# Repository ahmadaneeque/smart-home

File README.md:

# smart-home
dependencies 
- PainlessMesh to handel the mesh archetecture <https://github.com/gmag11/painlessMesh>
- WiFiManager to manage the credentials / https://github.com/tzapu/WiFiManager
- ArduinoJson to parse data https://github.com/bblanchon/ArduinoJson

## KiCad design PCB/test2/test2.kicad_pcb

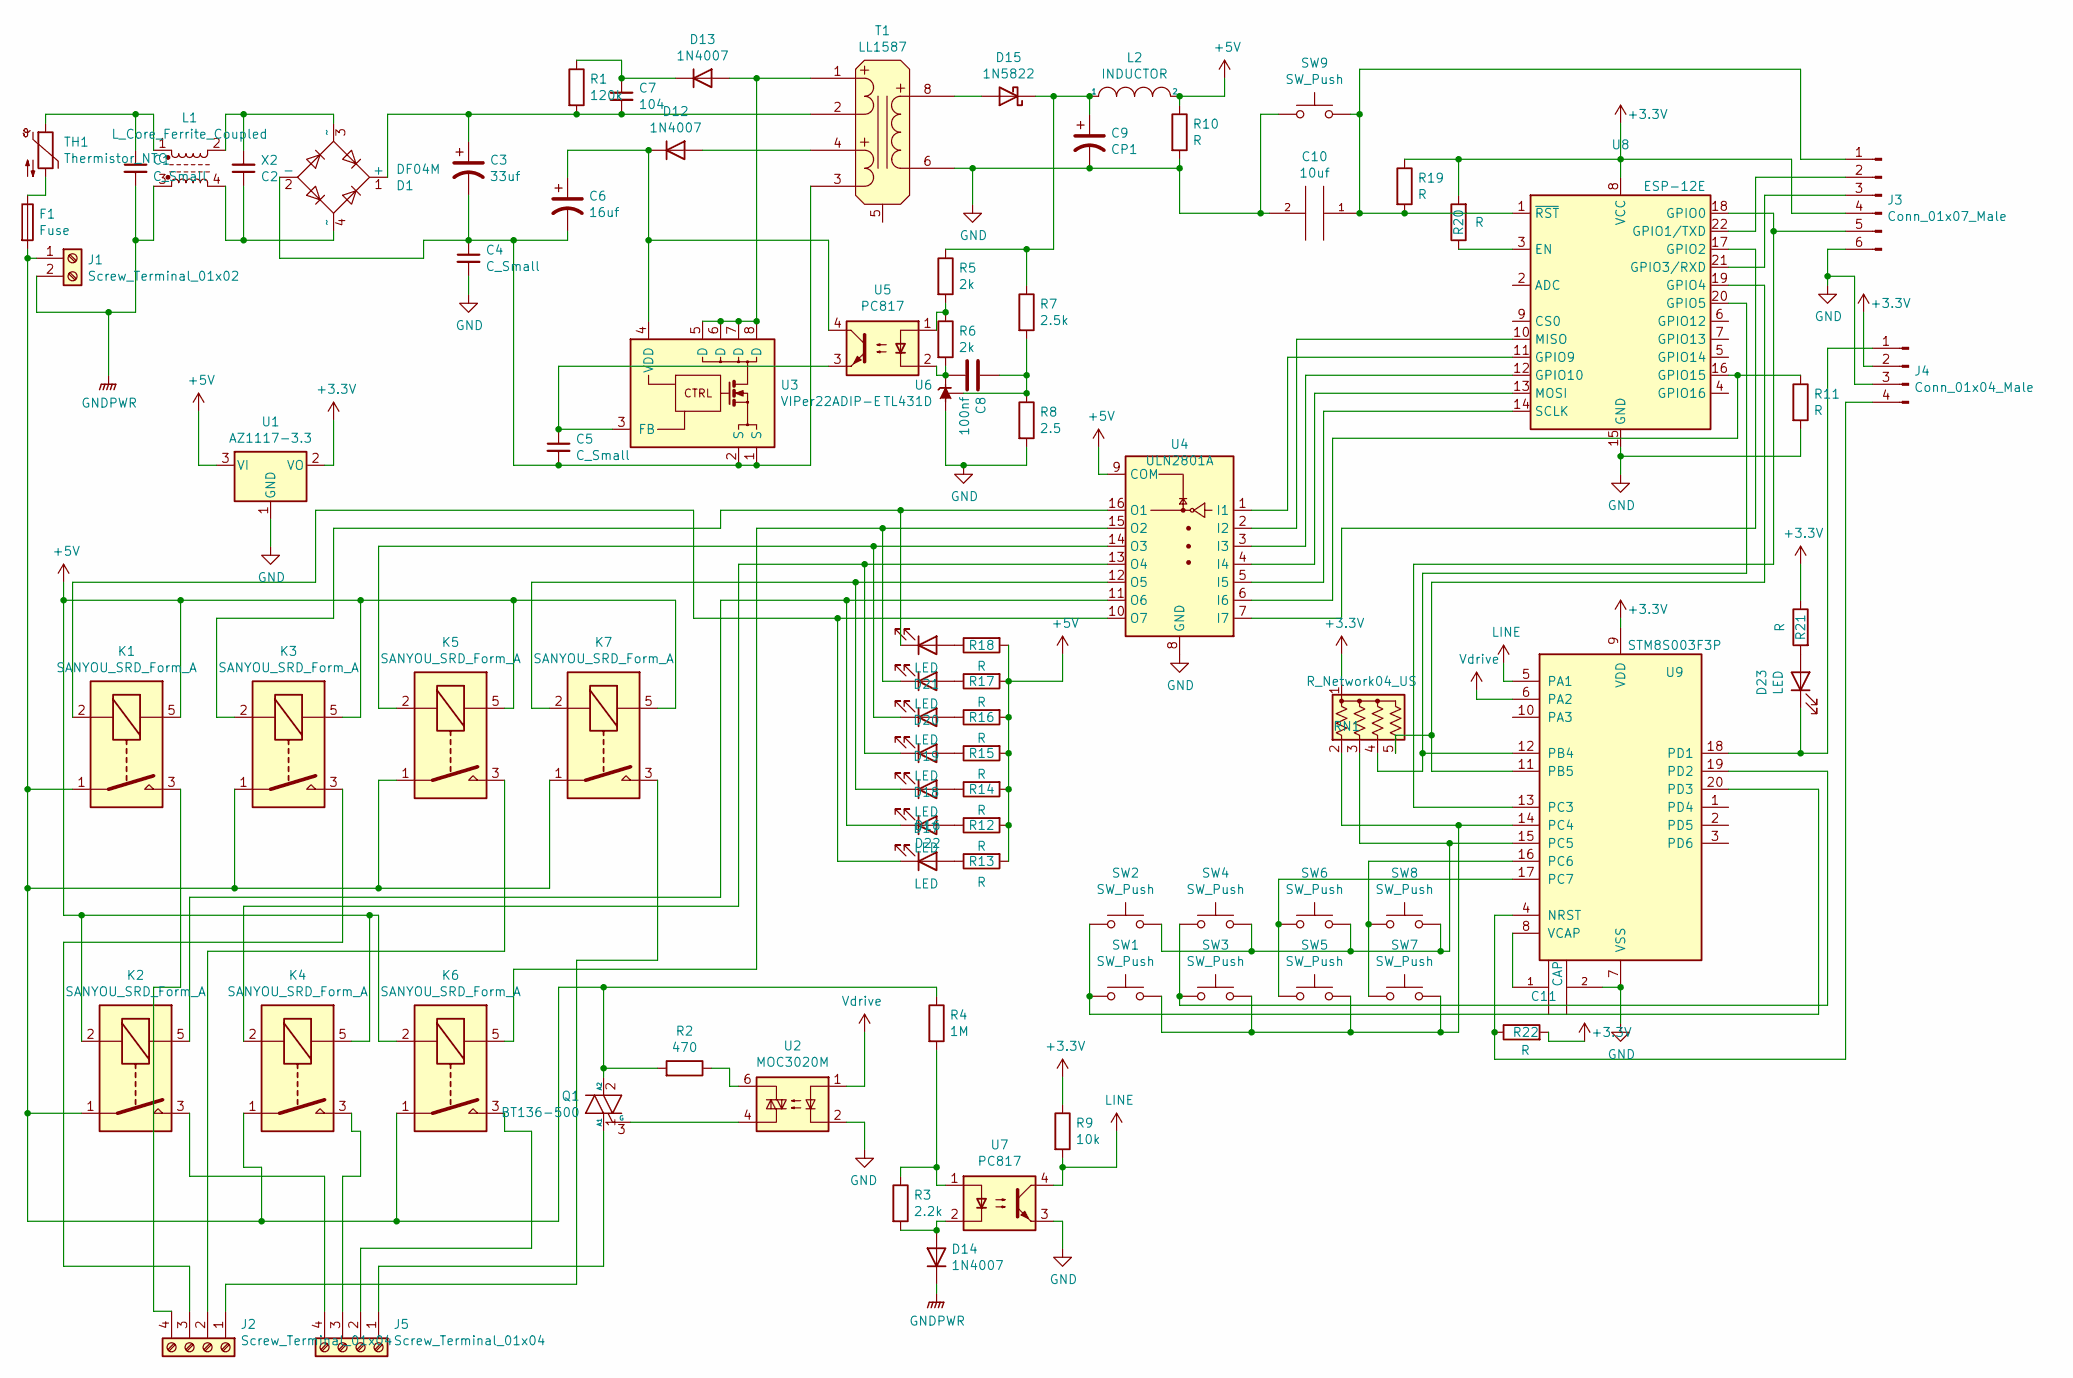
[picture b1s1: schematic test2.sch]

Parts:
C1: C_Small; RV_Disc_D7mm_W3.5mm_P5mm
C2: X2; CP_Axial_L10.0mm_D6.0mm_P15.00mm_Horizontal
C3: 33uf; CP_Radial_D10.0mm_P5.00mm_P7.50mm
C4: C_Small; C_Disc_D10.5mm_W5.0mm_P7.50mm
C5: C_Small; C_Disc_D4.3mm_W1.9mm_P5.00mm
C6: 16uf; CP_Radial_D4.0mm_P2.00mm
C7: 104; C_Disc_D4.3mm_W1.9mm_P5.00mm
C8: 100nf; C_Disc_D4.7mm_W2.5mm_P5.00mm
C9: CP1; CP_Radial_D8.0mm_P5.00mm
C10: 10uf; CP_Radial_D4.0mm_P2.00mm
C11: CAP; CP_Radial_D4.0mm_P2.00mm
D1: DF04M; Diode_Bridge_Vishay_DFS
D12, D14: 1N4007; D_DO-41_SOD81_P10.16mm_Horizontal
D13: 1N4007; D_DO-15_P3.81mm_Vertical_KathodeUp
D15: 1N5822; D_DO-201AD_P5.08mm_Vertical_KathodeUp
D16, D17, D18, D19, D20, D21, D22, D23: LED; LED_D3.0mm
F1: Fuse; Fuse_Bourns_MF-RHT200
J1: Screw_Terminal_01x02; Wago_734-132_1x02_P3.50mm_Vertical
J2, J5: Screw_Terminal_01x04; Wago_734-134_1x04_P3.50mm_Vertical
J3: Conn_01x07_Male; PinHeader_1x06_P2.54mm_Vertical
J4: Conn_01x04_Male; PinHeader_1x04_P2.54mm_Vertical
K1, K2, K3, K4, K5, K6, K7: SANYOU_SRD_Form_A; Relay_SPST_SANYOU_SRD_Series_Form_A
L1: L_Core_Ferrite_Coupled; Transformer_Toroid_Horizontal_D9.0mm_Amidon-T30
L2: INDUCTOR; L_Axial_L12.0mm_D5.0mm_P5.08mm_Vertical_Fastron_MISC
Q1: BT136-500; TO-220-3_Vertical
R1: 120k; R_Axial_DIN0204_L3.6mm_D1.6mm_P5.08mm_Horizontal
R2: 470; R_Axial_DIN0204_L3.6mm_D1.6mm_P7.62mm_Horizontal
R3: 2.2k; R_Axial_DIN0207_L6.3mm_D2.5mm_P7.62mm_Horizontal
R4: 1M; R_Axial_DIN0207_L6.3mm_D2.5mm_P7.62mm_Horizontal
R5, R6: 2k; R_Axial_DIN0204_L3.6mm_D1.6mm_P7.62mm_Horizontal
R7: 2.5k; R_Axial_DIN0207_L6.3mm_D2.5mm_P7.62mm_Horizontal
R8: 2.5; R_Axial_DIN0207_L6.3mm_D2.5mm_P7.62mm_Horizontal
R9: 10k; R_Axial_DIN0309_L9.0mm_D3.2mm_P12.70mm_Horizontal
R10, R12, R13, R14, R15, R16, R17, R18, R19, R20, R21, R22: R; R_Axial_DIN0204_L3.6mm_D1.6mm_P7.62mm_Horizontal
R11: R; R_0805_2012Metric
RN1: R_Network04_US; R_Array_SIP5
SW1, SW2, SW3, SW4, SW5, SW6, SW7, SW8, SW9: SW_Push; SW_Push_1P1T_NO_6x6mm_H9.5mm
T1: LL1587; 5v_1_A_flyback transformer 78_5_11
TH1: Thermistor_NTC; C_Disc_D7.0mm_W2.5mm_P5.00mm
U1: AZ1117-3.3; SOT-223
U2: MOC3020M; DIP-6_W8.89mm_SMDSocket_LongPads
U3: VIPer22ADIP-E; DIP-8_W7.62mm
U4: ULN2801A; DIP-16_W7.62mm_Socket_LongPads
U5: PC817; DIP-4_W7.62mm
U6: TL431D; TO-92_Inline_Wide
U7: PC817; DIP-4_W8.89mm_SMDSocket_LongPads
U8: ESP-12E
U9: STM8S003F3P; TSSOP-20_4.4x6.5mm_P0.65mm

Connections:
+3V3: J3.4, J4.2, R9.1, R19.1, R20.2, R21.1, R22.2, RN1.1 (common), U1.2 (VO), U8.8 (VCC), U9.9 (VDD)
+5V: K1.5, K2.2, K3.5, K4.5, K5.5, K6.2, K7.5, L2.2, R10.1, R12.2, R13.2, R14.2, R15.2, R16.2, R17.2, R18.2, U1.3 (VI), U4.9 (COM)
GND: C4.2, C9.2, C10.2, C11.2, J3.6, J4.3, R8.2, R10.2, R11.2, SW9.1, T1.6 (S-), U1.1 (GND), U2.2, U4.8 (GND), U6.2 (A), U7.3, U8.15 (GND), U9.7 (VSS)
GNDPWR: C1.2, D14.1 (K), J1.2, L1.3
LINE: R9.2, U7.4, U9.5 (PA1)
unnamed: C1.1, L1.1, TH1.1
unnamed: C2.1, D1.4 (~~), L1.4
unnamed: C2.2, D1.3 (~~), L1.2
unnamed: C3.1, C7.2, D1.1 (+), R1.2, T1.2 (P1-)
unnamed: C3.2, C4.1, C5.2, C6.2, D1.2 (-), T1.3 (P2-), U3.1 (S), U3.2 (S)
unnamed: C5.1, U3.3 (FB), U5.3
unnamed: C6.1, D12.1 (K), U3.4 (VDD), U5.4
unnamed: C7.1, D13.1 (K), R1.1
unnamed: C8.1, R7.2, R8.1, U6.1 (REF)
unnamed: C8.2, R6.2, U5.2, U6.3 (K)
unnamed: C9.1, D15.1 (K), L2.1, R5.1, R7.1
unnamed: C10.1, J3.1, R19.2, SW9.2, U8.1 (~RST)
unnamed: C11.1, U9.8 (VCAP)
unnamed: D12.2 (A), T1.4 (P2+)
unnamed: D13.2 (A), T1.1 (P1+), U3.5 (D), U3.6 (D), U3.7 (D), U3.8 (D)
unnamed: D14.2 (A), R3.2, U7.2
unnamed: D15.2 (A), T1.8 (S+)
unnamed: D16.1 (K), K2.5, U4.11 (O6)
unnamed: D16.2 (A), R12.1
unnamed: D17.1 (K), K7.2, U4.12 (O5)
unnamed: D17.2 (A), R14.1
unnamed: D18.1 (K), K4.2, U4.13 (O4)
unnamed: D18.2 (A), R15.1
unnamed: D19.1 (K), K5.2, U4.14 (O3)
unnamed: D19.2 (A), R16.1
unnamed: D20.1 (K), K6.5, U4.15 (O2)
unnamed: D20.2 (A), R17.1
unnamed: D21.1 (K), K3.2, U4.16 (O1)
unnamed: D21.2 (A), R18.1
unnamed: D22.1 (K), K1.2, U4.10 (O7)
unnamed: D22.2 (A), R13.1
unnamed: D23.1 (K), J4.1, U9.18 (PD1)
unnamed: D23.2 (A), R21.2
unnamed: F1.1, TH1.2
unnamed: F1.2, J1.1, K1.1, K2.1, K3.1, K4.1, K5.1, K6.1, K7.1, Q1.2 (A2), R2.2, R4.1
unnamed: J2.1, K7.3
unnamed: J2.2, K5.3
unnamed: J2.3, K3.3
unnamed: J2.4, K1.3
unnamed: J3.2, U8.22 (GPIO1/TXD)
unnamed: J3.3, U8.21 (GPIO3/RXD)
unnamed: J3.5, U8.18 (GPIO0), U9.13 (PC3)
unnamed: J4.4, R22.1, U9.4 (NRST)
unnamed: J5.1, Q1.1 (A1)
unnamed: J5.2, K6.3
unnamed: J5.3, K4.3
unnamed: J5.4, K2.3
unnamed: Q1.3 (G), U2.4
unnamed: R2.1, U2.6
unnamed: R3.1, R4.2, U7.1
unnamed: R5.2, R6.1, U5.1
unnamed: R11.1, U4.6 (I6), U8.16 (GPIO15)
unnamed: R20.1, U8.3 (EN)
unnamed: RN1.2 (R1), SW1.2, SW3.2, SW5.2, SW7.2, U9.14 (PC4)
unnamed: RN1.3 (R2), SW2.2, SW4.2, SW6.2, SW8.2, U9.15 (PC5)
unnamed: RN1.4 (R3), U8.20 (GPIO5), U9.12 (PB4)
unnamed: RN1.5 (R4), U8.19 (GPIO4), U9.11 (PB5)
unnamed: SW1.1, SW2.1, U9.20 (PD3)
unnamed: SW3.1, SW4.1, U9.19 (PD2)
unnamed: SW5.1, SW6.1, U9.17 (PC7)
unnamed: SW7.1, SW8.1, U9.16 (PC6)
unnamed: U4.1 (I1), U8.11 (GPIO9)
unnamed: U4.2 (I2), U8.10 (MISO)
unnamed: U4.3 (I3), U8.12 (GPIO10)
unnamed: U4.4 (I4), U8.13 (MOSI)
unnamed: U4.5 (I5), U8.14 (SCLK)
unnamed: U4.7 (I7), U8.17 (GPIO2)
Vdrive: U2.1, U9.6 (PA2)

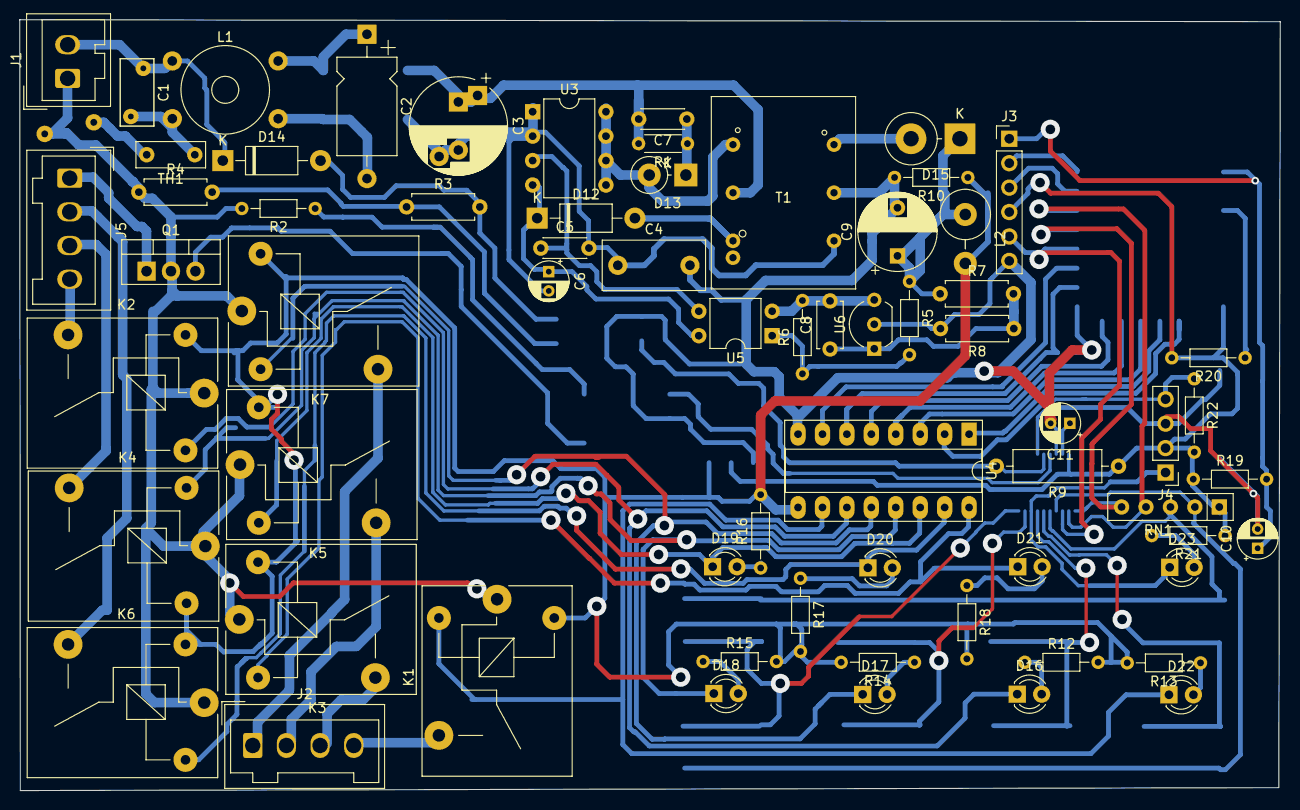
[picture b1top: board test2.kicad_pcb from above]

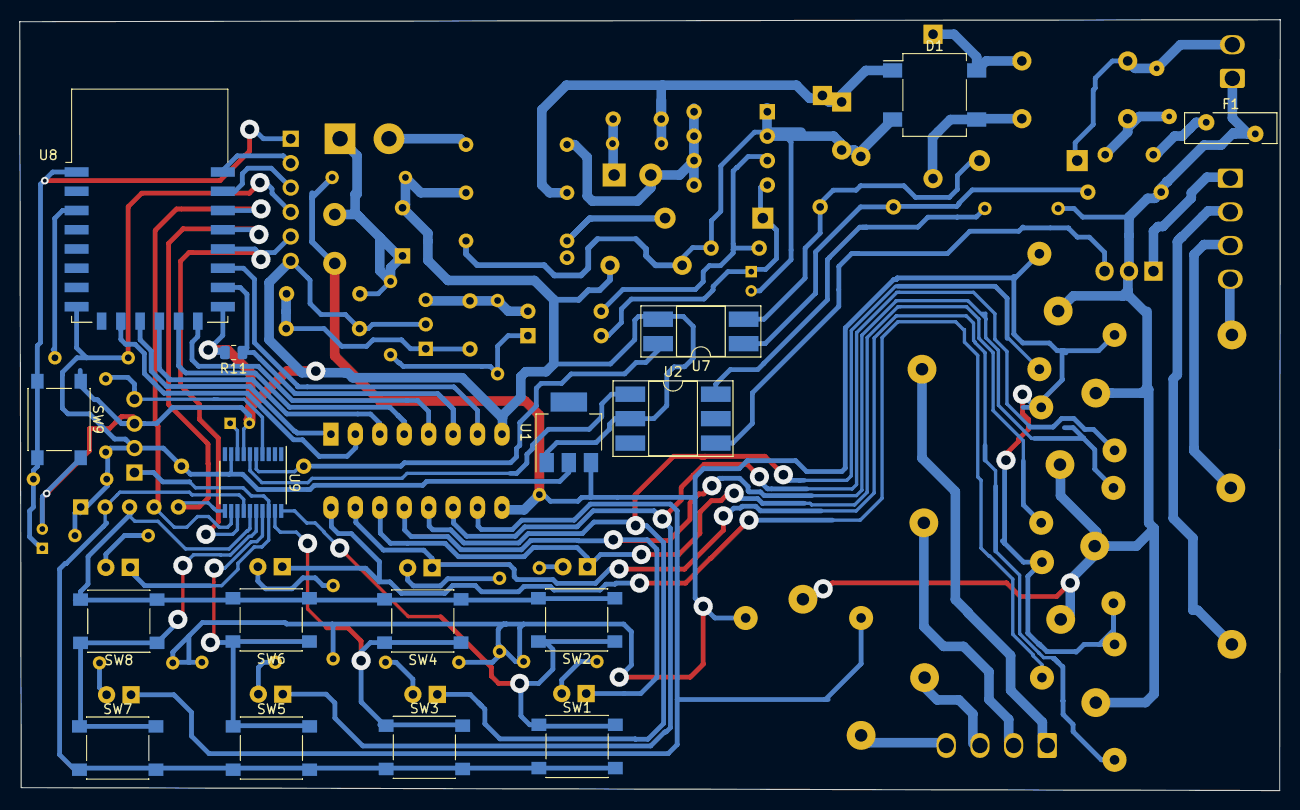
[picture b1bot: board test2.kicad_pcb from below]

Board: 2 copper layers, 131.0 x 80.1 mm, 83 parts (17 on the bottom side), 73 nets.

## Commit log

2020-08-14 addeed root node script for connection
2020-08-14 in code mqqt broker adding added
2020-09-04 added i2c master slave script
2021-09-11 check point
2021-09-12 added config structure for data handling
2021-09-12 config saving enable multiple publish removed
    remove hard coded credentials
2021-09-13 corrected the return statement
    file read function was returning false when succesful
2021-09-13 code refactor
    move config saving in side the readfile condition
2021-11-06 PCB using kiCad
